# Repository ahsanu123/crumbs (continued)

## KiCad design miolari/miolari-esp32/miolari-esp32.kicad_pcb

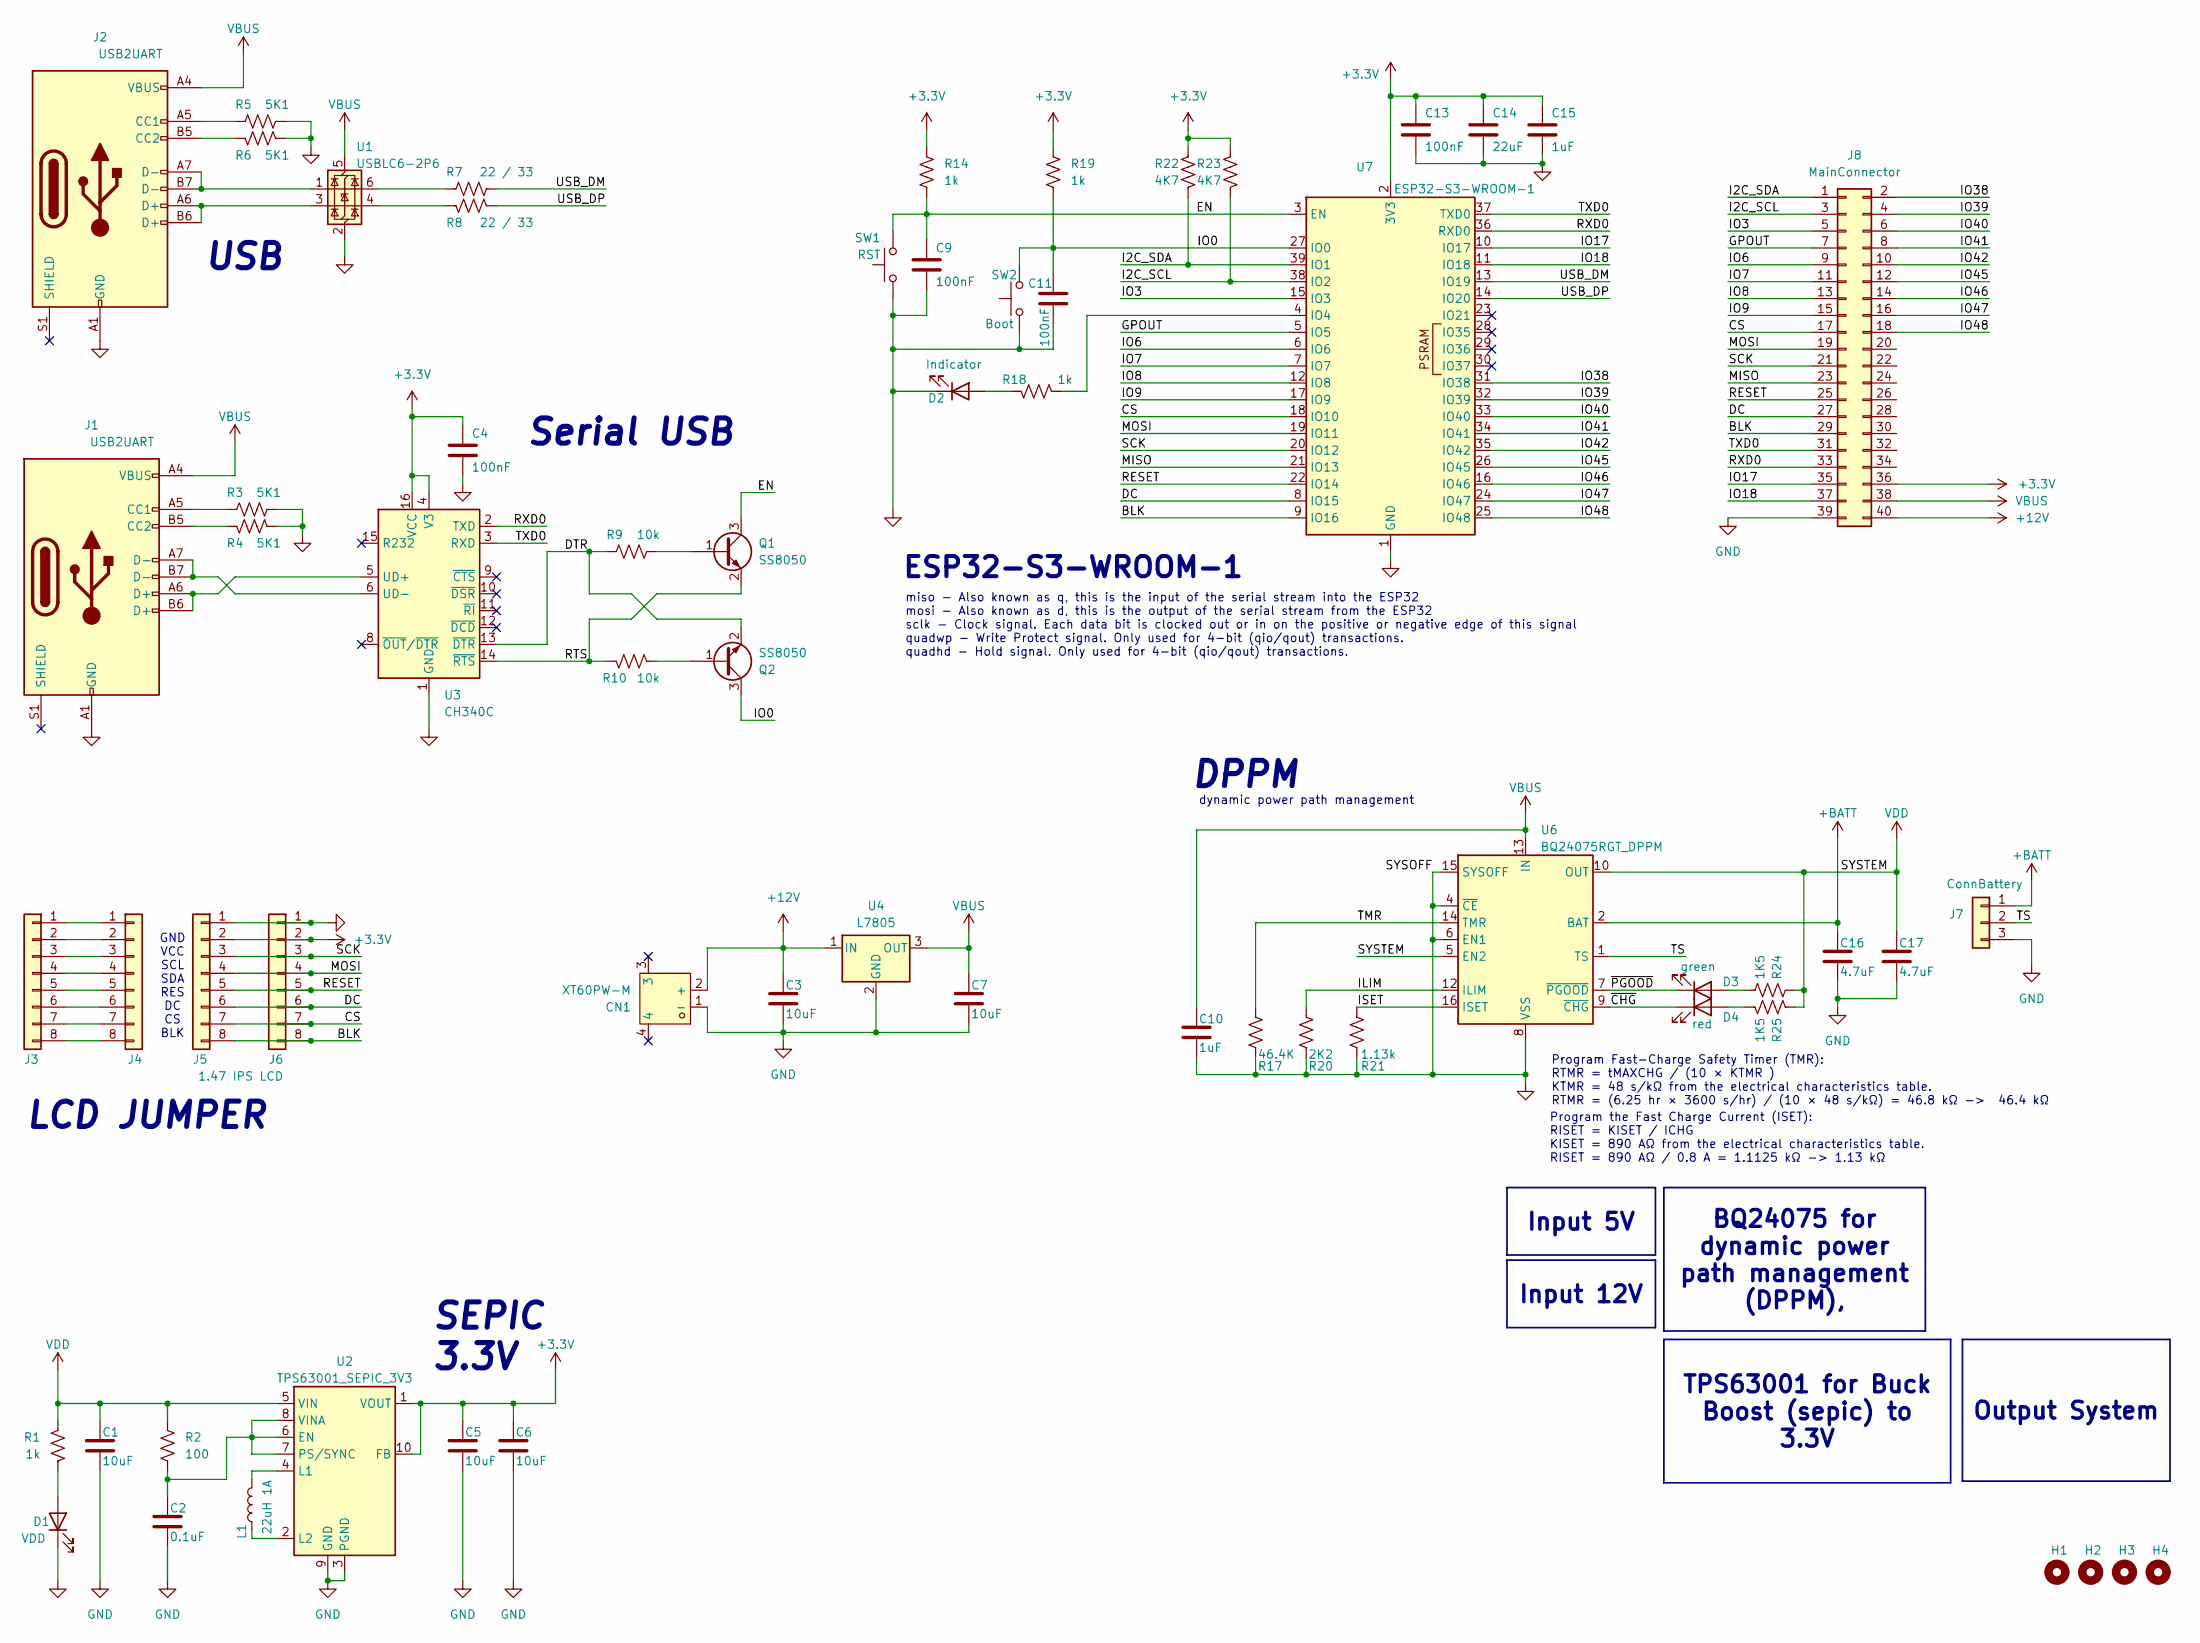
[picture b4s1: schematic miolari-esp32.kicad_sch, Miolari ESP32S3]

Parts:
C1, C3, C5, C6, C7: 10uF; C_0805_2012Metric_Pad1.18x1.45mm_HandSolder
C2: 0.1uF; C_0805_2012Metric_Pad1.18x1.45mm_HandSolder
C4, C9, C11, C13: 100nF; C_0805_2012Metric_Pad1.18x1.45mm_HandSolder
C10, C15: 1uF; C_0805_2012Metric_Pad1.18x1.45mm_HandSolder
C14: 22uF; C_0805_2012Metric_Pad1.18x1.45mm_HandSolder
C16, C17: 4.7uF; C_0805_2012Metric_Pad1.18x1.45mm_HandSolder
CN1: XT60PW-M; CONN-TH_XT60PW-M; MPN XT60PW-M; LCSC Part C98732
D1: VDD; LED_1206_3216Metric_Pad1.42x1.75mm_HandSolder
D2: Indicator; LED_1206_3216Metric_Pad1.42x1.75mm_HandSolder
D3: green; LED_0805_2012Metric_Pad1.15x1.40mm_HandSolder
D4: red; LED_0805_2012Metric_Pad1.15x1.40mm_HandSolder
H1, H2, H3, H4: MountingHole; MountingHole_2mm
J1, J2: USB2UART; USB_C_Receptacle_GCT_USB4110
J3, J4, J5: lcd jumper; PinHeader_1x08_P2.54mm_Vertical
J6: 1.47 IPS LCD; PinHeader_1x08_P2.54mm_Vertical
J7: ConnBattery; PinHeader_1x03_P2.54mm_Vertical
J8: MainConnector; IDC-Header_2x20_P2.54mm_Vertical
L1: 22uH 1A; L_Bourns_SRP7028A_7.3x6.6mm
Q1, Q2: SS8050; SOT-23_Handsoldering
R1, R14, R18, R19: 1k; R_0805_2012Metric_Pad1.20x1.40mm_HandSolder
R2: 100; R_0805_2012Metric_Pad1.20x1.40mm_HandSolder
R3, R4, R5, R6: 5K1; R_0805_2012Metric_Pad1.20x1.40mm_HandSolder
R7, R8: 22 / 33; R_0805_2012Metric_Pad1.20x1.40mm_HandSolder
R9, R10: 10k; R_0805_2012Metric_Pad1.20x1.40mm_HandSolder
R17: 46.4K; R_0805_2012Metric_Pad1.20x1.40mm_HandSolder
R20: 2K2; R_0805_2012Metric_Pad1.20x1.40mm_HandSolder
R21: 1.13k; R_0805_2012Metric_Pad1.20x1.40mm_HandSolder
R22, R23: 4K7; R_0805_2012Metric_Pad1.20x1.40mm_HandSolder
R24, R25: 1K5; R_0805_2012Metric_Pad1.20x1.40mm_HandSolder
SW1: RST; SW_SPST_EVQP7A
SW2: Boot; SW_SPST_EVQP7A
U1: USBLC6-2P6; SOT-666
U2: TPS63001_SEPIC_3V3; Texas_DRC0010J_ThermalVias
U3: CH340C; SOIC-16_3.9x9.9mm_P1.27mm
U4: L7805; TO-220-3_Horizontal_TabUp
U6: BQ24075RGT_DPPM; VQFN-16-1EP_3x3mm_P0.5mm_EP1.6x1.6mm
U7: ESP32-S3-WROOM-1

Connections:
+3.3V: C4.1, C5.1, C6.1, C13.1, C14.1, C15.1, J5.2, J6.2, J8.36, R14.1, R19.1, R22.1, R23.1, U2.1 (VOUT), U2.10 (FB), U3.4 (V3), U3.16 (VCC), U7.2 (3V3)
+12V: C3.1, CN1.2 (+), J8.40, U4.1 (IN)
+BATT: C16.1, J7.1, U6.2 (BAT), U6.3 (BAT)
/BLK: J5.8, J6.8, J8.29, U7.9 (IO16)
/CS: J5.7, J6.7, J8.17, U7.18 (IO10)
/DC: J5.6, J6.6, J8.27, U7.8 (IO15)
/DTR: Q2.2 (E), R9.2, U3.13 (~DTR)
/EN: C9.1, Q1.3 (C), R14.2, SW1.2, U7.3 (EN)
/GPOUT: J8.7, U7.5 (IO5)
/I2C_SCL: J8.3, R23.2, U7.38 (IO2)
/I2C_SDA: J8.1, R22.2, U7.39 (IO1)
/ILIM: R20.1, U6.12 (ILIM)
/IO0: C11.1, Q2.3 (C), R19.2, SW2.2, U7.27 (IO0)
/IO3: J8.5, U7.15 (IO3)
/IO6: J8.9, U7.6 (IO6)
/IO7: J8.11, U7.7 (IO7)
/IO8: J8.13, U7.12 (IO8)
/IO9: J8.15, U7.17 (IO9)
/IO17: J8.35, U7.10 (IO17)
/IO18: J8.37, U7.11 (IO18)
/IO38: J8.2, U7.31 (IO38)
/IO39: J8.4, U7.32 (IO39)
/IO40: J8.6, U7.33 (IO40)
/IO41: J8.8, U7.34 (IO41)
/IO42: J8.10, U7.35 (IO42)
/IO45: J8.12, U7.26 (IO45)
/IO46: J8.14, U7.16 (IO46)
/IO47: J8.16, U7.24 (IO47)
/IO48: J8.18, U7.25 (IO48)
/ISET: R21.1, U6.16 (ISET)
/MISO: J8.23, U7.21 (IO13)
/MOSI: J5.4, J6.4, J8.19, U7.19 (IO11)
/RESET: J5.5, J6.5, J8.25, U7.22 (IO14)
/RTS: Q1.2 (E), R10.2, U3.14 (~RTS)
/RXD0: J8.33, U3.2 (TXD), U7.36 (RXD0)
/SCK: J5.3, J6.3, J8.21, U7.20 (IO12)
/TMR: R17.1, U6.14 (TMR)
/TS: J7.2, U6.1 (TS)
/TXD0: J8.31, U3.3 (RXD), U7.37 (TXD0)
/USB_DM: R7.1, U7.13 (IO19)
/USB_DP: R8.1, U7.14 (IO20)
/~CHG: D4.1 (K), U6.9 (~CHG)
/~PGOOD: D3.1 (K), U6.7 (~PGOOD)
GND: C1.2, C2.2, C3.2, C4.2, C5.2, C6.2, C7.2, C9.2, C10.2, C11.2, C13.2, C14.2, C15.2, C16.2, C17.2, CN1.1 (-), D1.1 (K), D2.1 (K), J1.A1 (GND), J1.A12 (GND), J1.B1 (GND), J1.B12 (GND), J2.A1 (GND), J2.A12 (GND), J2.B1 (GND), J2.B12 (GND), J5.1, J6.1, J7.3, J8.39, R3.1, R4.1, R5.1, R6.1, R17.2, R20.2, R21.2, SW1.1, SW2.1, U1.2 (GND), U2.3 (PGND), U2.9 (GND), U2.11 (PGND), U3.1 (GND), U4.2 (GND), U6.4 (~CE), U6.6 (EN1), U6.8 (VSS), U6.15 (SYSOFF), U6.17 (VSS), U7.1 (GND), U7.40 (GND), U7.41 (GND)
unnamed: D1.2 (A), R1.2
unnamed: D2.2 (A), R18.1
unnamed: D3.2 (A), R24.1
unnamed: D4.2 (A), R25.1
unnamed: J1.A5 (CC1), R3.2
unnamed: J1.B5 (CC2), R4.2
unnamed: J2.A5 (CC1), R5.2
unnamed: J2.B5 (CC2), R6.2
unnamed: J2.A6 (D+), J2.B6 (D+), U1.3 (I/O2)
unnamed: J2.A7 (D-), J2.B7 (D-), U1.1 (I/O1)
unnamed: J3.1, J4.1
unnamed: J3.2, J4.2
unnamed: J3.3, J4.3
unnamed: J3.4, J4.4
unnamed: J3.5, J4.5
unnamed: J3.6, J4.6
unnamed: J3.7, J4.7
unnamed: J3.8, J4.8
unnamed: Q1.1 (B), R9.1
unnamed: Q2.1 (B), R10.1
unnamed: R7.2, U1.6 (I/O1)
unnamed: R8.2, U1.4 (I/O2)
unnamed: C2.1, R2.2, U2.6 (EN), U2.7 (PS/SYNC), U2.8 (VINA)
unnamed: L1.2, U2.4 (L1)
unnamed: L1.1, U2.2 (L2)
unnamed: J1.A6 (D+), J1.B6 (D+), U3.5 (UD+)
unnamed: J1.A7 (D-), J1.B7 (D-), U3.6 (UD-)
unnamed: R18.2, U7.4 (IO4)
VBUS: C7.1, C10.1, J1.A4 (VBUS), J1.A9 (VBUS), J1.B4 (VBUS), J1.B9 (VBUS), J2.A4 (VBUS), J2.A9 (VBUS), J2.B4 (VBUS), J2.B9 (VBUS), J8.38, U1.5 (VBUS), U4.3 (OUT), U6.13 (IN)
VDD: C1.1, C17.1, R1.1, R2.1, R24.2, R25.2, U2.5 (VIN), U6.5 (EN2), U6.10 (OUT), U6.11 (OUT)

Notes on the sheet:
USB
DPPM
Serial USB
GND VCC SCL SDA RES DC CS BLK
Program Fast-Charge Safety Timer (TMR): RTMR = tMAXCHG / (10 × KTMR ) KTMR = 48 s/kΩ from the electrical characteristics table. RTMR = (6.25 hr × 3600 s/hr) / (10 × 48 s/kΩ) = 46.8 kΩ -> 46.4 kΩ
ESP32-S3-WROOM-1
miso - Also known as q, this is the input of the serial stream into the ESP32 mosi - Also known as d, this is the output of the serial stream from the ESP32 sclk - Clock signal. Each data bit is clocked out or in on the positive or negative edge of this signal quadwp - Write Protect signal. Only us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
dynamic power path management
SEPIC 3.3V
LCD JUMPER
Program the Fast Charge Current (ISET): RISET = KISET / ICHG KISET = 890 AΩ from the electrical characteristics table. RISET = 890 AΩ / 0.8 A = 1.1125 kΩ -> 1.13 kΩ
Output System
BQ24075 for dynamic power path management (DPPM),
Input 5V
TPS63001 for Buck Boost (sepic) to 3.3V
Input 12V

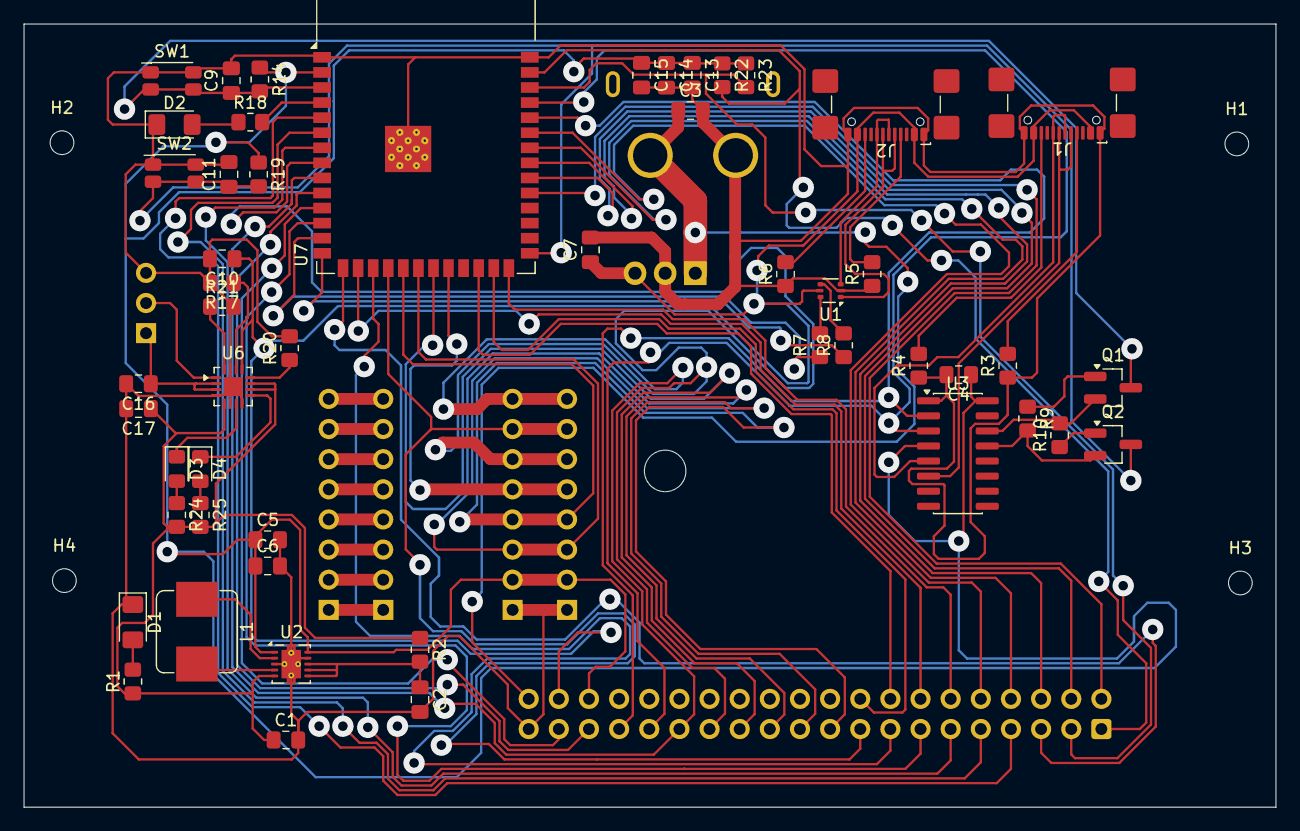
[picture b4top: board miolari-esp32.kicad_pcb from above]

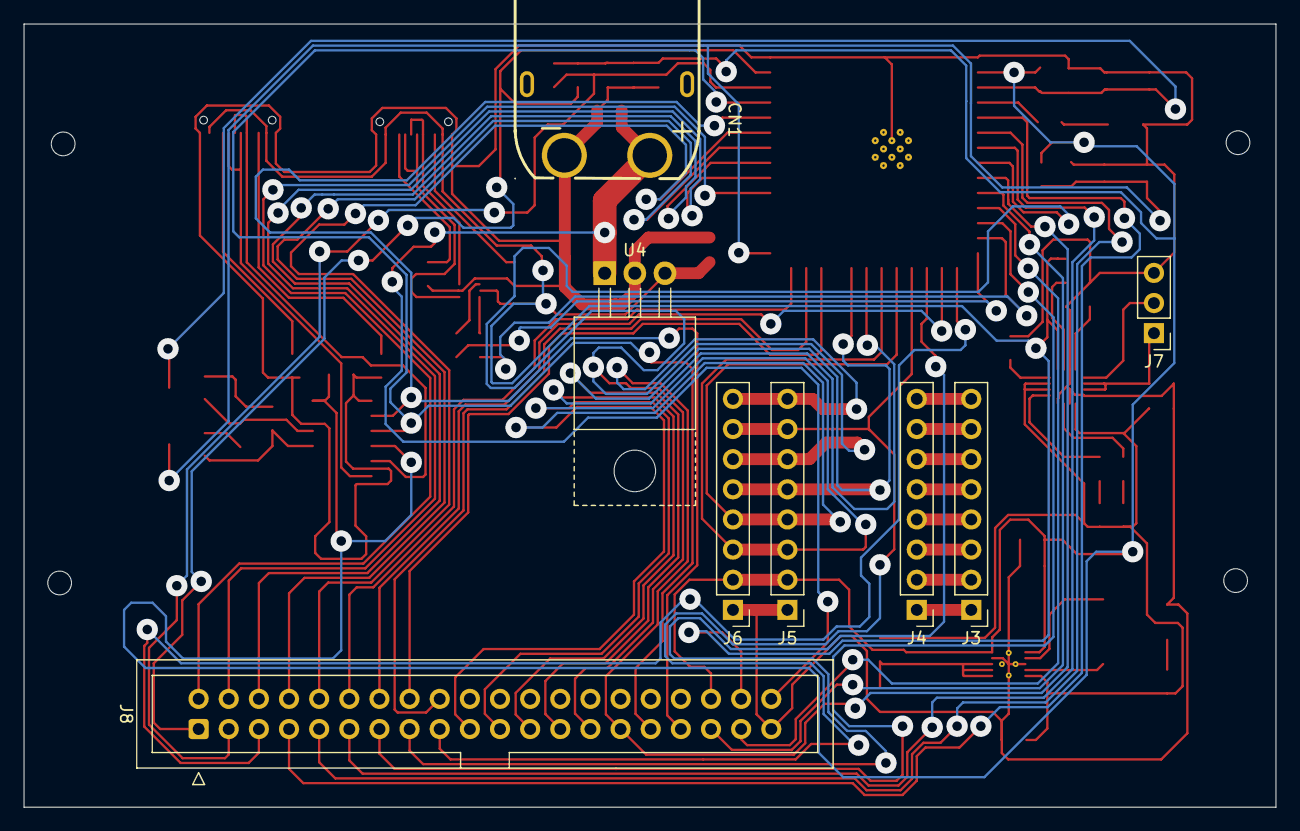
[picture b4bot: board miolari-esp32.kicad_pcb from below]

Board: 2 copper layers, 105.5 x 66.0 mm, 63 parts (8 on the bottom side), 74 nets.

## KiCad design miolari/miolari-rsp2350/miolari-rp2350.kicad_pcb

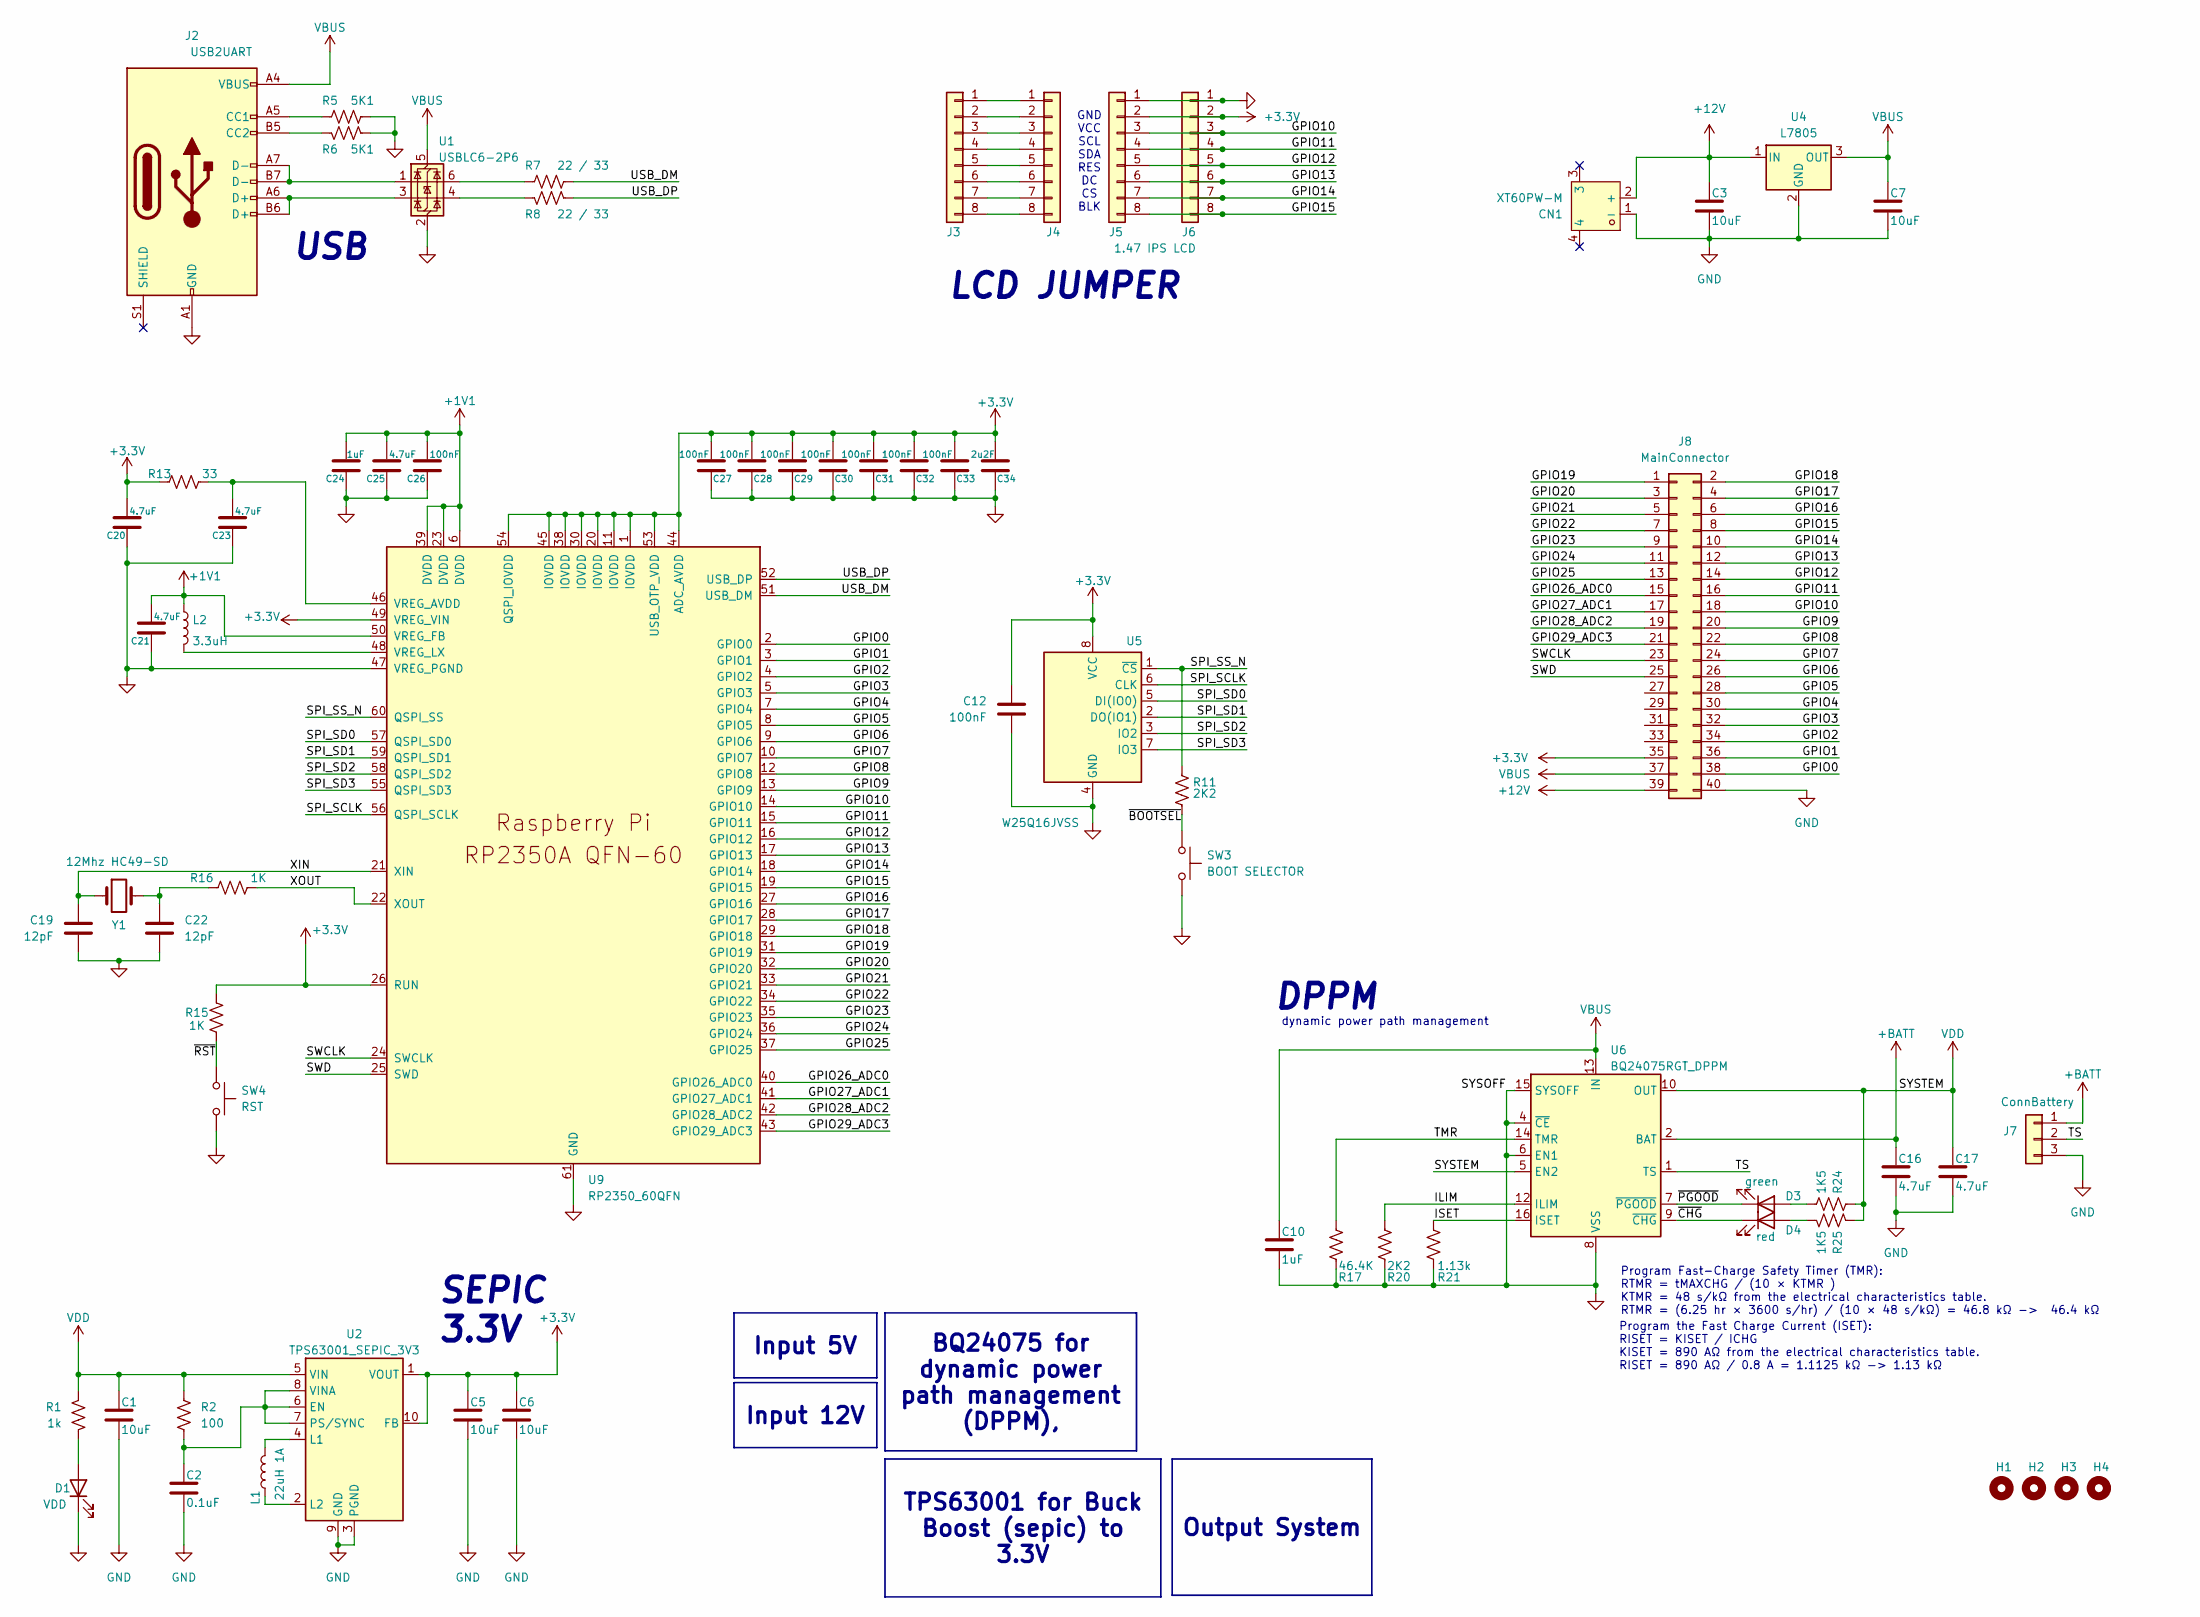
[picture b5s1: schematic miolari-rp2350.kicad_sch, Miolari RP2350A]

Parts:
C1, C3, C5, C6, C7: 10uF; C_0805_2012Metric_Pad1.18x1.45mm_HandSolder
C2: 0.1uF; C_0805_2012Metric_Pad1.18x1.45mm_HandSolder
C10: 1uF; C_0805_2012Metric_Pad1.18x1.45mm_HandSolder
C12, C26, C27, C28, C29, C30, C31, C32, C33: 100nF; C_0603_1608Metric_Pad1.08x0.95mm_HandSolder
C16, C17: 4.7uF; C_0805_2012Metric_Pad1.18x1.45mm_HandSolder
C19, C22: 12pF; C_0603_1608Metric_Pad1.08x0.95mm_HandSolder
C20, C21, C23, C25: 4.7uF; C_0603_1608Metric_Pad1.08x0.95mm_HandSolder
C24: 1uF; C_0603_1608Metric_Pad1.08x0.95mm_HandSolder
C34: 2u2F; C_0603_1608Metric_Pad1.08x0.95mm_HandSolder
CN1: XT60PW-M; CONN-TH_XT60PW-M; MPN XT60PW-M; LCSC Part C98732
D1: VDD; LED_1206_3216Metric_Pad1.42x1.75mm_HandSolder
D3: green; LED_0805_2012Metric_Pad1.15x1.40mm_HandSolder
D4: red; LED_0805_2012Metric_Pad1.15x1.40mm_HandSolder
H1, H2, H3, H4: MountingHole; MountingHole_2mm
J2: USB2UART; USB_C_Receptacle_GCT_USB4110
J3, J4, J5: lcd jumper; PinHeader_1x08_P2.54mm_Vertical
J6: 1.47 IPS LCD; PinHeader_1x08_P2.54mm_Vertical
J7: ConnBattery; PinHeader_1x03_P2.54mm_Vertical
J8: MainConnector; IDC-Header_2x20_P2.54mm_Vertical
L1: 22uH 1A; L_Bourns_SRP7028A_7.3x6.6mm
L2: 3.3uH; L_0805_2012Metric_Pad1.05x1.20mm_HandSolder
R1: 1k; R_0805_2012Metric_Pad1.20x1.40mm_HandSolder
R2: 100; R_0805_2012Metric_Pad1.20x1.40mm_HandSolder
R5, R6: 5K1; R_0805_2012Metric_Pad1.20x1.40mm_HandSolder
R7, R8: 22 / 33; R_0805_2012Metric_Pad1.20x1.40mm_HandSolder
R11, R20: 2K2; R_0805_2012Metric_Pad1.20x1.40mm_HandSolder
R13: 33; R_0805_2012Metric_Pad1.20x1.40mm_HandSolder
R15, R16: 1K; R_0805_2012Metric_Pad1.20x1.40mm_HandSolder
R17: 46.4K; R_0805_2012Metric_Pad1.20x1.40mm_HandSolder
R21: 1.13k; R_0805_2012Metric_Pad1.20x1.40mm_HandSolder
R24, R25: 1K5; R_0805_2012Metric_Pad1.20x1.40mm_HandSolder
SW3: BOOT SELECTOR; SW_Push_1P1T_NO_CK_KMR2
SW4: RST; SW_Push_1P1T_NO_CK_KMR2
U1: USBLC6-2P6; SOT-666
U2: TPS63001_SEPIC_3V3; Texas_DRC0010J_ThermalVias
U4: L7805; TO-220-3_Horizontal_TabUp
U5: W25Q16JVSS; SOIC-8_5.3x5.3mm_P1.27mm
U6: BQ24075RGT_DPPM; VQFN-16-1EP_3x3mm_P0.5mm_EP1.6x1.6mm
U9: RP2350_60QFN; RP2350-QFN-60-1EP_7x7_P0.4mm_EP3.4x3.4mm_ThermalVias
Y1: 12Mhz HC49-SD; Crystal_SMD_HC49-SD

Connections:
+1V1: C21.1, C24.1, C25.1, C26.1, L2.1, U9.6 (DVDD), U9.23 (DVDD), U9.39 (DVDD), U9.50 (VREG_FB)
+3.3V: C5.1, C6.1, C12.1, C20.1, C27.1, C28.1, C29.1, C30.1, C31.1, C32.1, C33.1, C34.1, J5.2, J6.2, J8.35, R13.1, R15.2, U2.1 (VOUT), U2.10 (FB), U5.8 (VCC), U9.1 (IOVDD), U9.11 (IOVDD), U9.20 (IOVDD), U9.26 (RUN), U9.30 (IOVDD), U9.38 (IOVDD), U9.44 (ADC_AVDD), U9.45 (IOVDD), U9.49 (VREG_VIN), U9.53 (USB_OTP_VDD), U9.54 (QSPI_IOVDD)
+12V: C3.1, CN1.2 (+), J8.39, U4.1 (IN)
+BATT: C16.1, J7.1, U6.2 (BAT), U6.3 (BAT)
/GPIO0: J8.38, U9.2 (GPIO0)
/GPIO1: J8.36, U9.3 (GPIO1)
/GPIO2: J8.34, U9.4 (GPIO2)
/GPIO3: J8.32, U9.5 (GPIO3)
/GPIO4: J8.30, U9.7 (GPIO4)
/GPIO5: J8.28, U9.8 (GPIO5)
/GPIO6: J8.26, U9.9 (GPIO6)
/GPIO7: J8.24, U9.10 (GPIO7)
/GPIO8: J8.22, U9.12 (GPIO8)
/GPIO9: J8.20, U9.13 (GPIO9)
/GPIO10: J5.3, J6.3, J8.18, U9.14 (GPIO10)
/GPIO11: J5.4, J6.4, J8.16, U9.15 (GPIO11)
/GPIO12: J5.5, J6.5, J8.14, U9.16 (GPIO12)
/GPIO13: J5.6, J6.6, J8.12, U9.17 (GPIO13)
/GPIO14: J5.7, J6.7, J8.10, U9.18 (GPIO14)
/GPIO15: J5.8, J6.8, J8.8, U9.19 (GPIO15)
/GPIO16: J8.6, U9.27 (GPIO16)
/GPIO17: J8.4, U9.28 (GPIO17)
/GPIO18: J8.2, U9.29 (GPIO18)
/GPIO19: J8.1, U9.31 (GPIO19)
/GPIO20: J8.3, U9.32 (GPIO20)
/GPIO21: J8.5, U9.33 (GPIO21)
/GPIO22: J8.7, U9.34 (GPIO22)
/GPIO23: J8.9, U9.35 (GPIO23)
/GPIO24: J8.11, U9.36 (GPIO24)
/GPIO25: J8.13, U9.37 (GPIO25)
/GPIO26_ADC0: J8.15, U9.40 (GPIO26_ADC0)
/GPIO27_ADC1: J8.17, U9.41 (GPIO27_ADC1)
/GPIO28_ADC2: J8.19, U9.42 (GPIO28_ADC2)
/GPIO29_ADC3: J8.21, U9.43 (GPIO29_ADC3)
/ILIM: R20.1, U6.12 (ILIM)
/ISET: R21.1, U6.16 (ISET)
/SPI_SCLK: U5.6 (CLK), U9.56 (QSPI_SCLK)
/SPI_SD0: U5.5 (DI(IO0)), U9.57 (QSPI_SD0)
/SPI_SD1: U5.2 (DO(IO1)), U9.59 (QSPI_SD1)
/SPI_SD2: U5.3 (IO2), U9.58 (QSPI_SD2)
/SPI_SD3: U5.7 (IO3), U9.55 (QSPI_SD3)
/SPI_SS_N: R11.1, U5.1 (~CS), U9.60 (QSPI_SS)
/SWCLK: J8.23, U9.24 (SWCLK)
/SWD: J8.25, U9.25 (SWD)
/TMR: R17.1, U6.14 (TMR)
/TS: J7.2, U6.1 (TS)
/USB_DM: R7.1, U9.51 (USB_DM)
/USB_DP: R8.1, U9.52 (USB_DP)
/XIN: C19.1, U9.21 (XIN), Y1.1
/XOUT: R16.2, U9.22 (XOUT)
/~BOOTSEL: R11.2, SW3.1
/~CHG: D4.1 (K), U6.9 (~CHG)
/~PGOOD: D3.1 (K), U6.7 (~PGOOD)
/~RST: R15.1, SW4.1
GND: C1.2, C2.2, C3.2, C5.2, C6.2, C7.2, C10.2, C12.2, C16.2, C17.2, C19.2, C20.2, C21.2, C22.2, C23.2, C24.2, C25.2, C26.2, C27.2, C28.2, C29.2, C30.2, C31.2, C32.2, C33.2, C34.2, CN1.1 (-), D1.1 (K), J2.A1 (GND), J2.A12 (GND), J2.B1 (GND), J2.B12 (GND), J5.1, J6.1, J7.3, J8.40, R5.1, R6.1, R17.2, R20.2, R21.2, SW3.2, SW4.2, U1.2 (GND), U2.3 (PGND), U2.9 (GND), U2.11 (PGND), U4.2 (GND), U5.4 (GND), U6.4 (~CE), U6.6 (EN1), U6.8 (VSS), U6.15 (SYSOFF), U6.17 (VSS), U9.47 (VREG_PGND), U9.61 (GND)
unnamed: C22.1, R16.1, Y1.2
unnamed: D1.2 (A), R1.2
unnamed: D3.2 (A), R24.1
unnamed: D4.2 (A), R25.1
unnamed: J2.A5 (CC1), R5.2
unnamed: J2.B5 (CC2), R6.2
unnamed: J2.A6 (D+), J2.B6 (D+), U1.3 (I/O2)
unnamed: J2.A7 (D-), J2.B7 (D-), U1.1 (I/O1)
unnamed: J3.1, J4.1
unnamed: J3.2, J4.2
unnamed: J3.3, J4.3
unnamed: J3.4, J4.4
unnamed: J3.5, J4.5
unnamed: J3.6, J4.6
unnamed: J3.7, J4.7
unnamed: J3.8, J4.8
unnamed: R7.2, U1.6 (I/O1)
unnamed: R8.2, U1.4 (I/O2)
unnamed: C2.1, R2.2, U2.6 (EN), U2.7 (PS/SYNC), U2.8 (VINA)
unnamed: L1.2, U2.4 (L1)
unnamed: L1.1, U2.2 (L2)
unnamed: C23.1, R13.2, U9.46 (VREG_AVDD)
unnamed: L2.2, U9.48 (VREG_LX)
VBUS: C7.1, C10.1, J2.A4 (VBUS), J2.A9 (VBUS), J2.B4 (VBUS), J2.B9 (VBUS), J8.37, U1.5 (VBUS), U4.3 (OUT), U6.13 (IN)
VDD: C1.1, C17.1, R1.1, R2.1, R24.2, R25.2, U2.5 (VIN), U6.5 (EN2), U6.10 (OUT), U6.11 (OUT)

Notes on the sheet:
USB
DPPM
GND VCC SCL SDA RES DC CS BLK
Program Fast-Charge Safety Timer (TMR): RTMR = tMAXCHG / (10 × KTMR ) KTMR = 48 s/kΩ from the electrical characteristics table. RTMR = (6.25 hr × 3600 s/hr) / (10 × 48 s/kΩ) = 46.8 kΩ -> 46.4 kΩ
dynamic power path management
SEPIC 3.3V
LCD JUMPER
Program the Fast Charge Current (ISET): RISET = KISET / ICHG KISET = 890 AΩ from the electrical characteristics table. RISET = 890 AΩ / 0.8 A = 1.1125 kΩ -> 1.13 kΩ
Output System
BQ24075 for dynamic power path management (DPPM),
Input 5V
TPS63001 for Buck Boost (sepic) to 3.3V
Input 12V

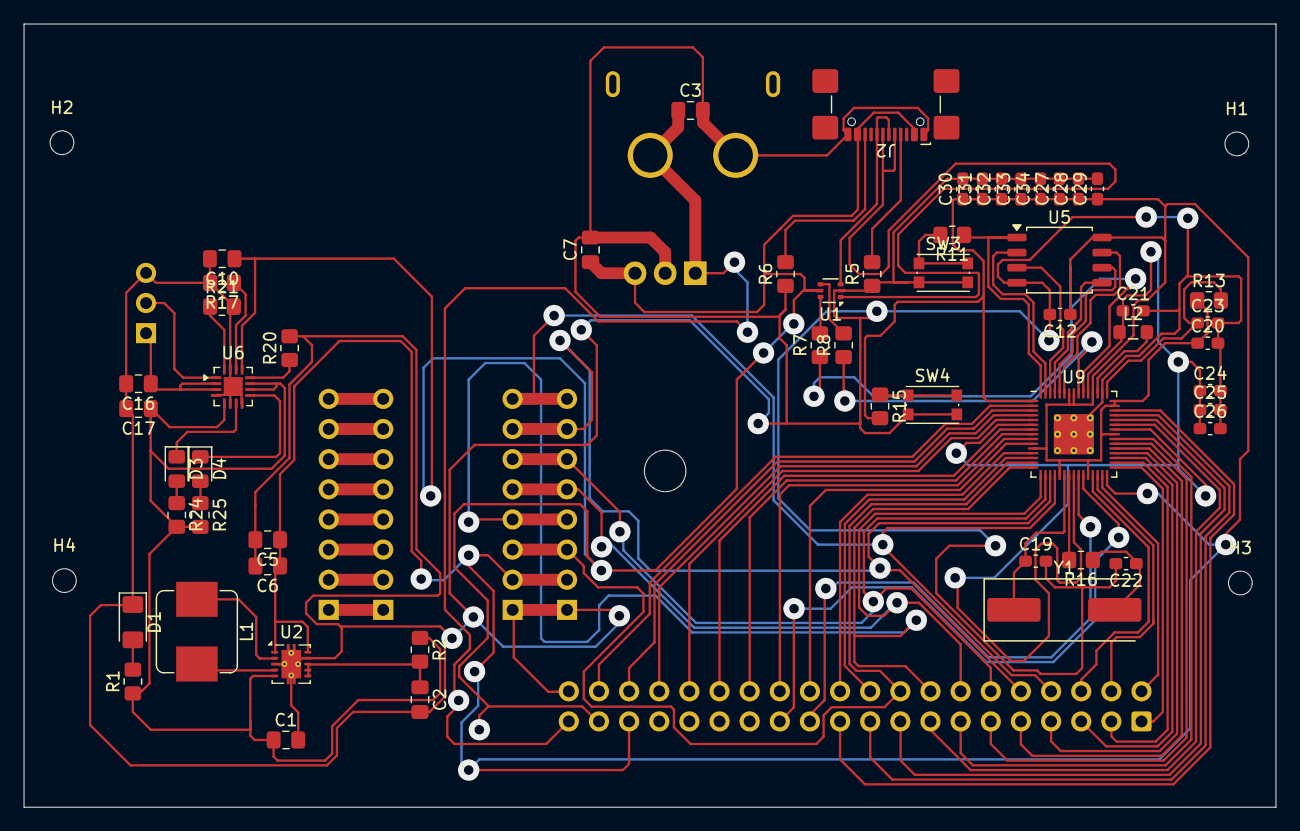
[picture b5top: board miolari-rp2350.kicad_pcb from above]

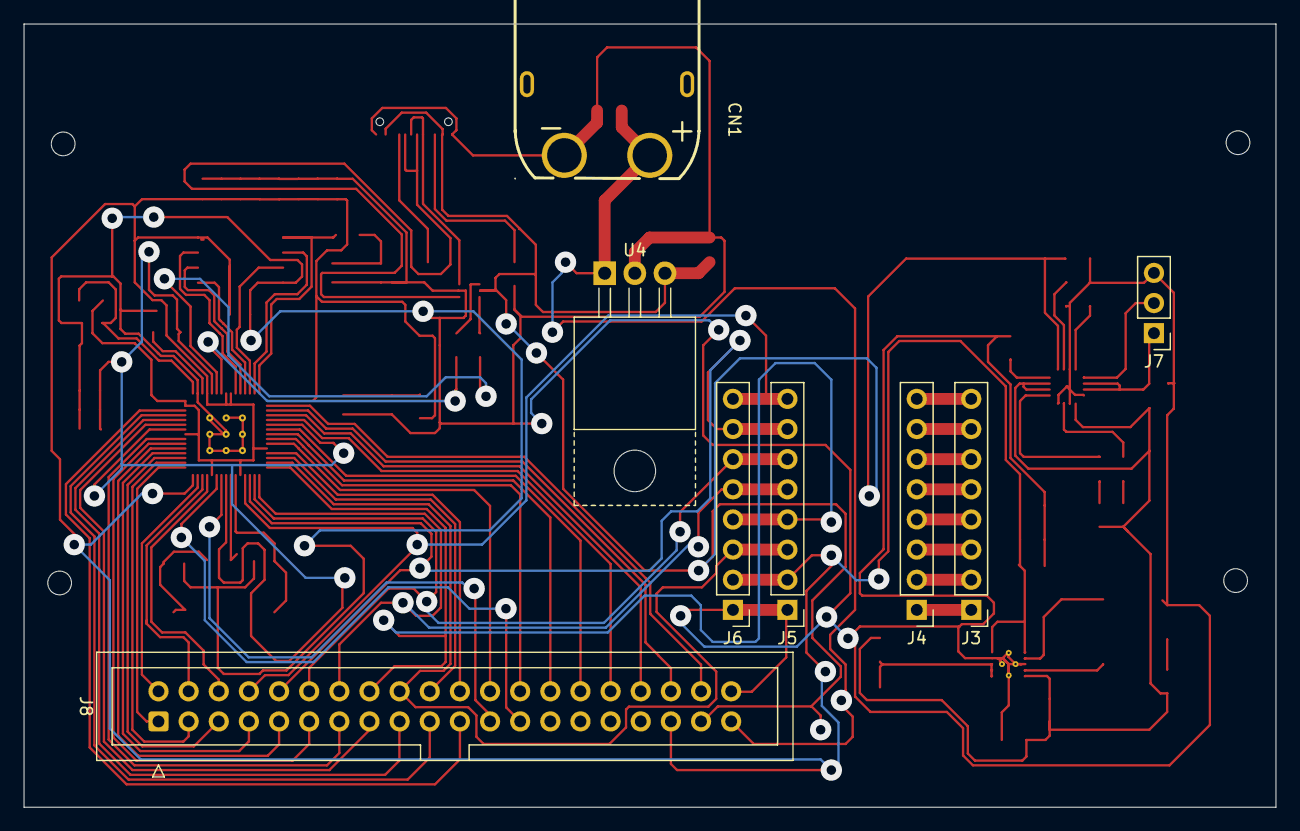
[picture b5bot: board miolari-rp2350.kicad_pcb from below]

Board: 2 copper layers, 105.5 x 66.0 mm, 67 parts (8 on the bottom side), 80 nets.
